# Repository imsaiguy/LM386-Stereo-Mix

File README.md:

# LM386-Stereo-Mix
eagle files for stereo headphone mixter
gerber zip file

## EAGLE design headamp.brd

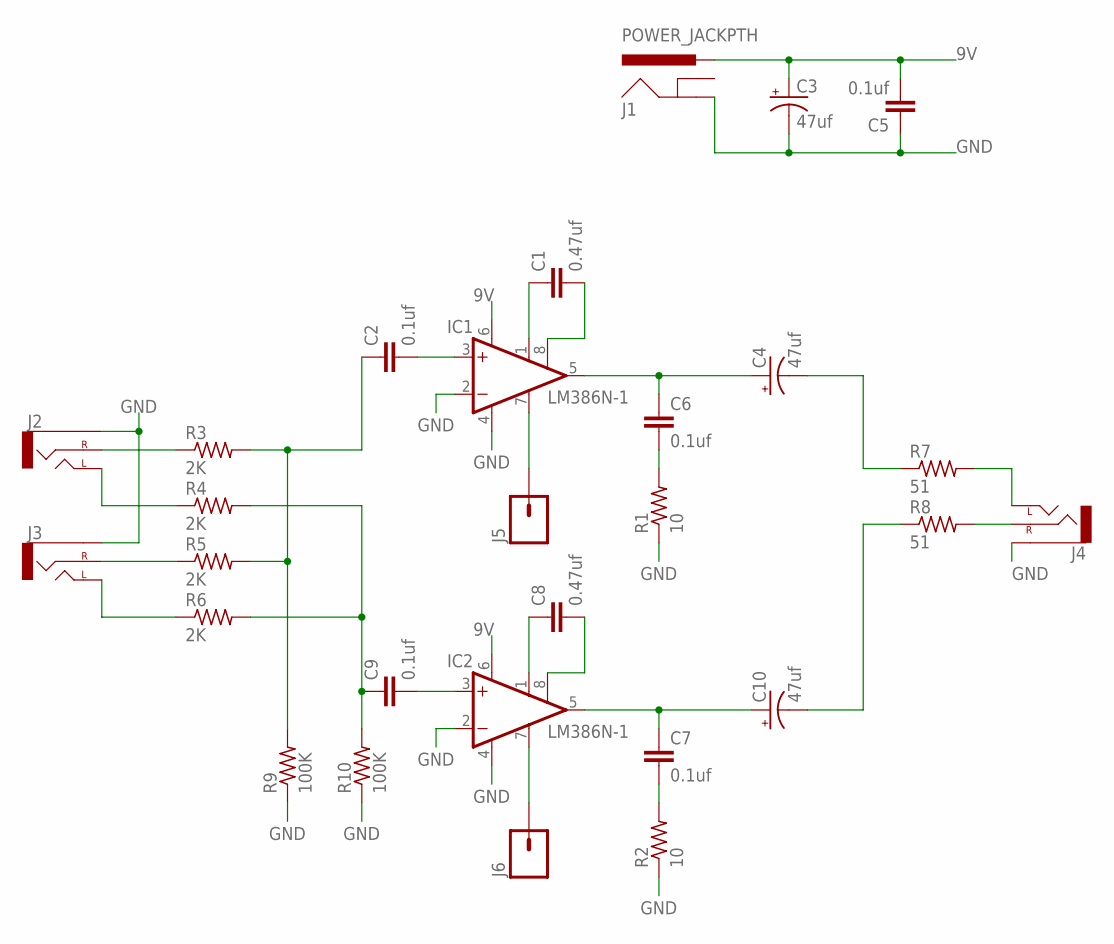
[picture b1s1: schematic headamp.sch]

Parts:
C1, C8: 0.47uf; 1210
C2, C5, C6, C7, C9: 0.1uf; 1210
C3, C4, C10: 47uf; CPOL-RADIAL-100UF-25V
IC1, IC2: LM386N-1; DIL08
J1: POWER_JACKPTH; POWER_JACK_PTH
J2, J3, J4: AUDIO-JACKPTH; AUDIO-JACK
J5, J6: M01NOSILK-KIT; 1X01NS-KIT
R1, R2: 10; M0805
R3, R4, R5, R6: 2K; M0805
R7, R8: 51; M0805
R9, R10: 100K; M0805

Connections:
9V: C3.1 (+), C5.2, IC1.6 (VS), IC2.6 (VS), J1.PWR
GND: C3.2 (-), C5.1, IC1.2 (-IN), IC1.4 (GND), IC2.2 (-IN), IC2.4 (GND), J1.GND, J2.SLEEVE, J3.SLEEVE, J4.SLEEVE, R1.1, R2.1, R9.1, R10.1
LEFT: C2.1, R3.2, R5.2, R9.2
unnamed: C1.1, IC1.1 (GAIN)
unnamed: C1.2, IC1.8 (GAIN)
unnamed: C2.2, IC1.3 (+IN)
unnamed: IC1.7 (BYPASS), J5.1
unnamed: J4.RING (RIGHT), R8.2
unnamed: J4.TIP (LEFT), R7.2
unnamed: C4.2 (-), R7.1
unnamed: C4.1 (+), C6.1, IC1.5 (OUT)
unnamed: J2.RING (RIGHT), R3.1
unnamed: J2.TIP (LEFT), R4.1
unnamed: J3.RING (RIGHT), R5.1
unnamed: J3.TIP (LEFT), R6.1
unnamed: C6.2, R1.2
unnamed: C10.2 (-), R8.1
unnamed: C8.1, IC2.1 (GAIN)
unnamed: C8.2, IC2.8 (GAIN)
unnamed: C9.2, IC2.3 (+IN)
unnamed: C7.1, C10.1 (+), IC2.5 (OUT)
unnamed: C7.2, R2.2
unnamed: IC2.7 (BYPASS), J6.1
RIGHT: C9.1, R4.2, R6.2, R10.2

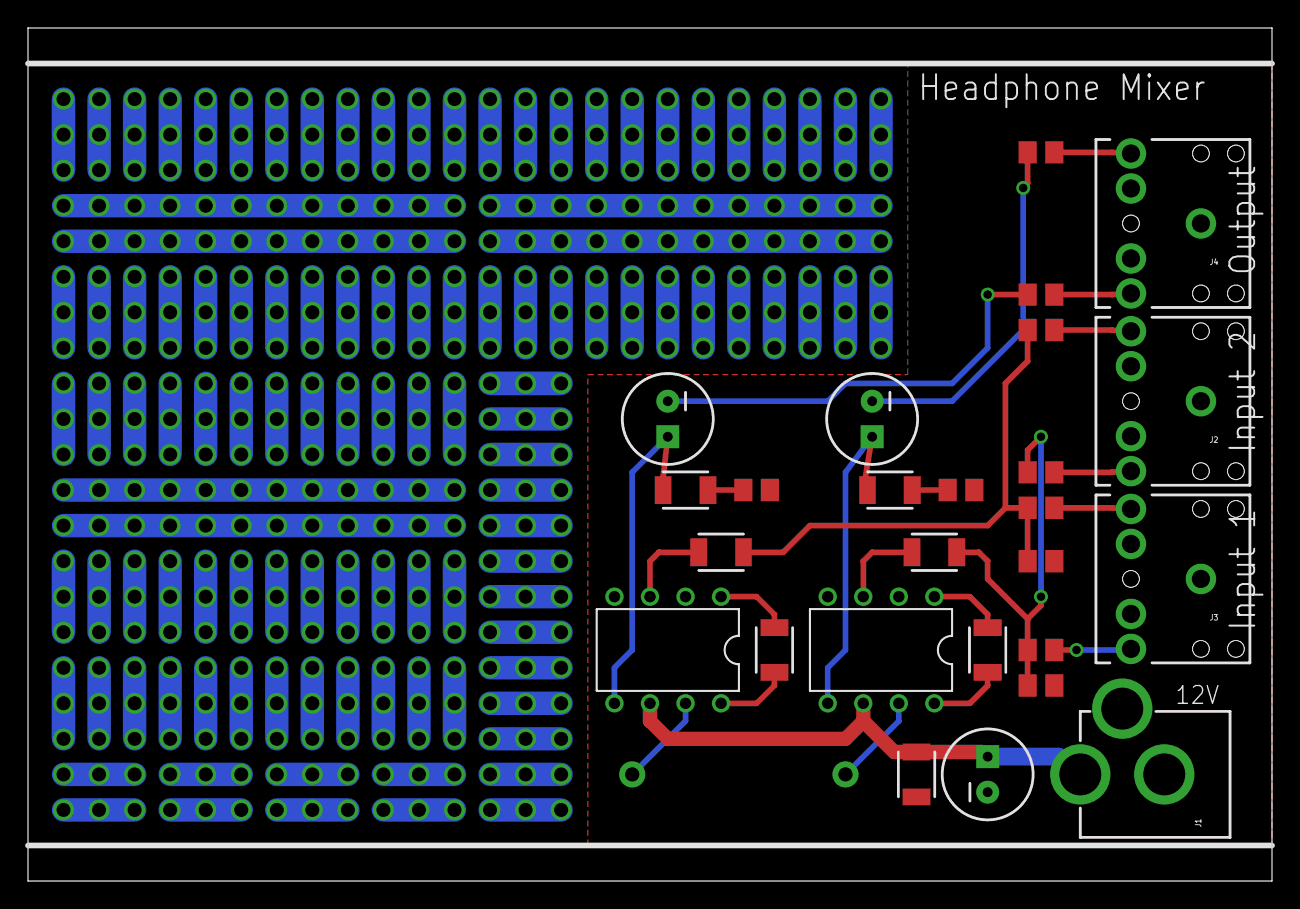
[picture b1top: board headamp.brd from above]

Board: 2 copper layers, 88.9 x 61.0 mm, 28 parts (0 on the bottom side), 24 nets.

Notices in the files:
parts and their libraries:
SparkFun-Capacitors: Licensing: Creative Commons ShareAlike 4.0 International - https://creativecommons.org/licenses/by-sa/4.0
